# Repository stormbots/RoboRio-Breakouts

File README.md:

# RoboRio Breakout Boards
Helpful boards for simplifying wiring and reducing splicing when connecting sensors to the RoboRio

## Sonar
This board is intended to connect with 4 wire sonar sensors. Details are present in the [Sonar](./Sonar Breakouts/) folder. 

## Encoders
This board is intended to connect with quadrature encoders. Details are present in the [Encoder](./Encoder Breakouts/) folder.

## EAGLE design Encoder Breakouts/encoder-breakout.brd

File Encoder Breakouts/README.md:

# Encoder Breakouts
This board simply converts a the 2 1x3 headers into a single 1x4 header for reduced splicing and cable connections. 

## Wiring Guidelines
To remain consistent with FRC wiring guidelines, it's suggested to use a 4 wire cable with the following order:

- Black
- Red
- Any
- Any

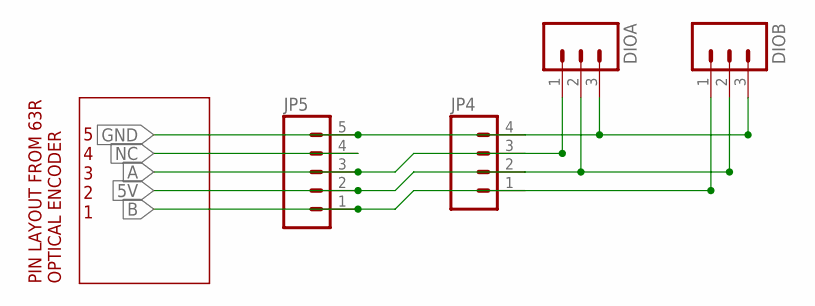
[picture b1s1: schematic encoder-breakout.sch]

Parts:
DIOA: M03LOCK; 1X03_LOCK
DIOB: M03LOCK; 1X03_LOCK
JP4: M04LOCK; 1X04_LOCK
JP5: M05LOCK; 1X05_LOCK

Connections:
5V: DIOA.2, DIOB.2, JP4.2, JP5.2
A: DIOA.1, JP4.3, JP5.3
B: DIOB.1, JP4.1, JP5.1
GND: DIOA.3, DIOB.3, JP4.4, JP5.5
NC: JP5.4

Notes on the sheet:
PIN LAYOUT FROM 63R OPTICAL ENCODER
5 4 3 2 1

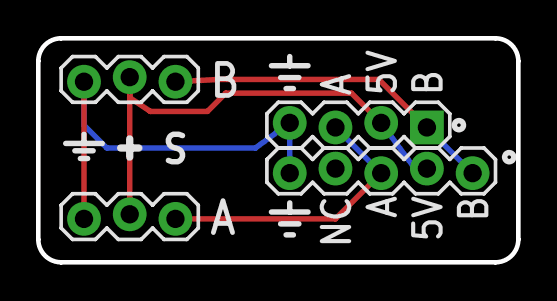
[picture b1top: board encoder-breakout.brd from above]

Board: 2 copper layers, 26.7 x 12.4 mm, 4 parts (0 on the bottom side), 4 nets.

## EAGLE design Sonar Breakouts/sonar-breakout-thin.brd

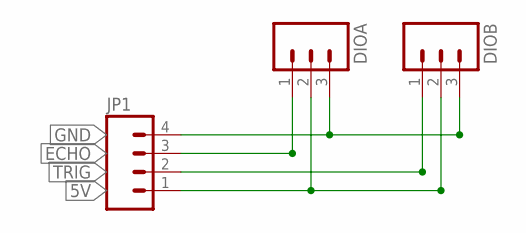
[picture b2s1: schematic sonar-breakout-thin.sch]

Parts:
DIOA: M03LOCK; 1X03_LOCK
DIOB: M03LOCK; 1X03_LOCK
JP1: M04LOCK; 1X04_LOCK

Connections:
5V: DIOA.2, DIOB.2, JP1.1
ECHO: DIOA.1, JP1.3
GND: DIOA.3, DIOB.3, JP1.4
TRIG: DIOB.1, JP1.2

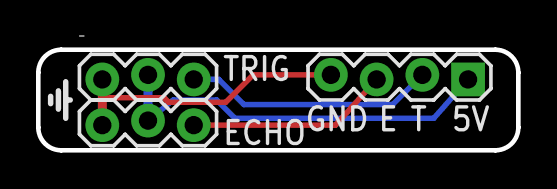
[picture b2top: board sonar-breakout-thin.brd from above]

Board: 2 copper layers, 26.7 x 6.2 mm, 3 parts (0 on the bottom side), 4 nets.

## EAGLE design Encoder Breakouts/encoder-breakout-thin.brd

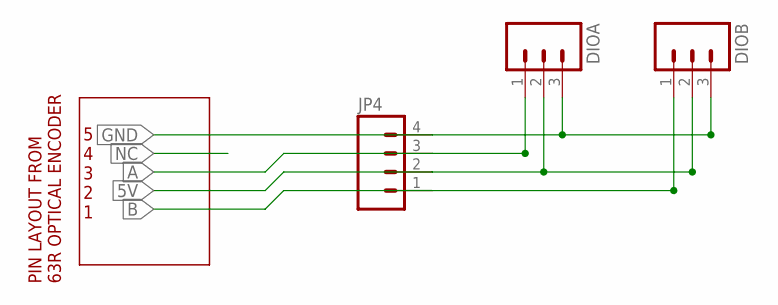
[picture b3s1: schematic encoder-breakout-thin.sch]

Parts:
DIOA: M03LOCK; 1X03_LOCK
DIOB: M03LOCK; 1X03_LOCK
JP4: M04LOCK; 1X04_LOCK

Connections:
5V: DIOA.2, DIOB.2, JP4.2
A: DIOA.1, JP4.3
B: DIOB.1, JP4.1
GND: DIOA.3, DIOB.3, JP4.4

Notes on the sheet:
PIN LAYOUT FROM 63R OPTICAL ENCODER
5 4 3 2 1

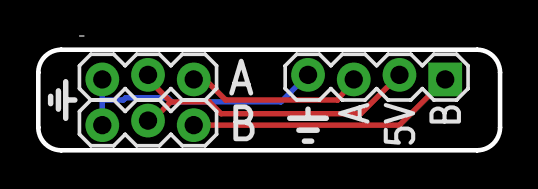
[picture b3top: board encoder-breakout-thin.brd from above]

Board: 2 copper layers, 25.7 x 6.2 mm, 3 parts (0 on the bottom side), 4 nets.

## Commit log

2016-06-19 Working version
2016-06-19 Fix links

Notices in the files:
parts and their libraries:
SparkFun-Connectors: Licensing: Creative Commons ShareAlike 4.0 International - https://creativecommons.org/licenses/by-sa/4.0
